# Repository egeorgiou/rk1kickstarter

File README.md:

# rk1kickstarter
RK1 Kickstarter Project

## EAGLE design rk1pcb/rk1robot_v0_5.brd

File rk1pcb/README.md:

rk1pcb
======

rk1 eagle pcb design

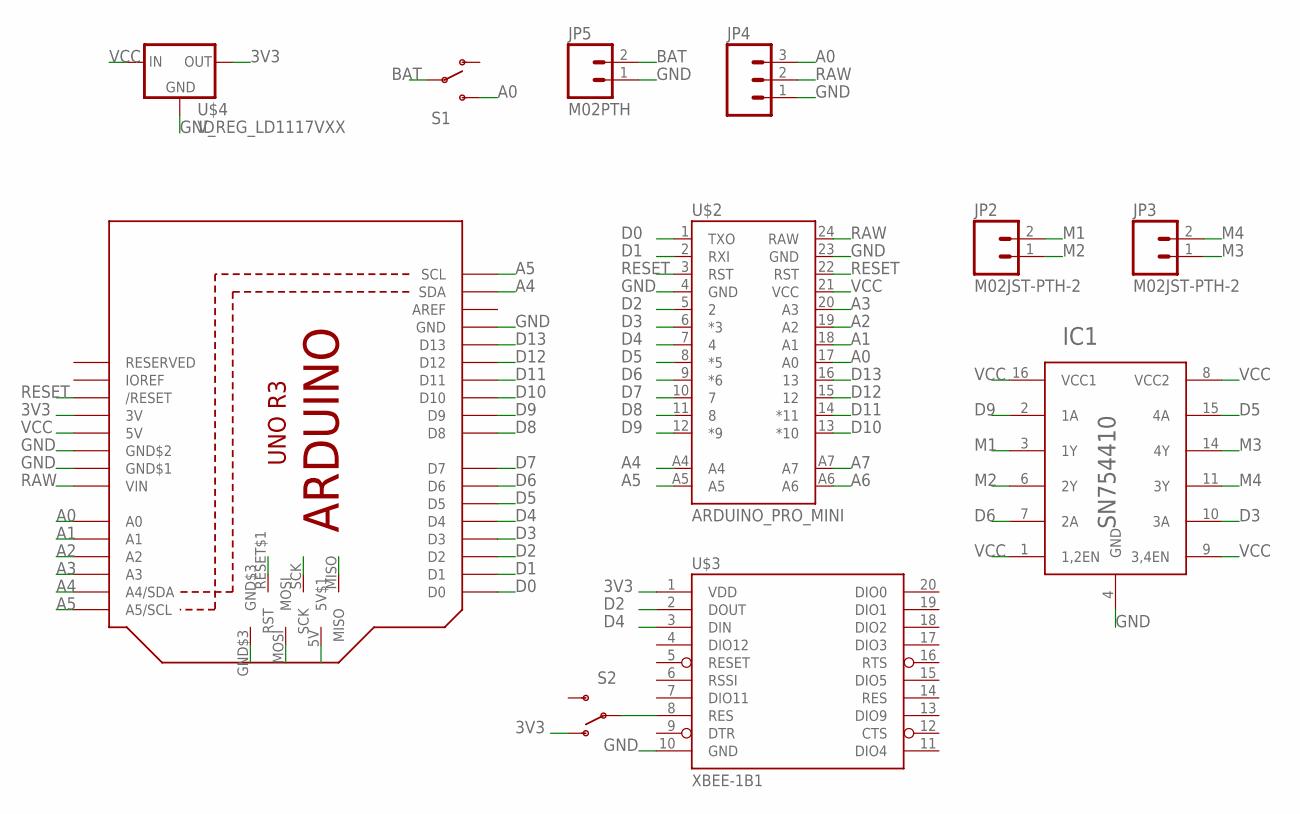
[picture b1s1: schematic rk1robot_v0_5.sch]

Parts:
IC1: SN754410; DIL16
JP2, JP3: M02JST-PTH-2; JST-2-PTH
JP4: M03PTH; 1X03
JP5: M02PTH; 1X02
S1, S2: SWITCH-SPDTPTH; SWITCH-SPDT
U$1: ARDUINO_R3_ICSP; ARDUINOR3_ICSP
U$2: ARDUINO_PRO_MINI
U$3: XBEE-1B1; XBEE-1
U$4: V_REG_LD1117VXX; 78XXL

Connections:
3V3: S2.1 (O), U$1.3V, U$3.1 (VDD), U$4.GND (OUT)
A0: JP4.3, S1.3 (S), U$1.A0, U$2.17 (A0)
A1: U$1.A1, U$2.18 (A1)
A2: U$1.A2, U$2.19 (A2)
A3: U$1.A3, U$2.20 (A3)
A4: U$1.A4 (A4/SDA), U$1.SDA, U$2.A4
A5: U$1.A5 (A5/SCL), U$1.SCL, U$2.A5
A6: U$2.A6
A7: U$2.A7
BAT: JP5.2, S1.2
D0: U$1.D0, U$2.1 (TXO)
D1: U$1.D1, U$2.2 (RXI)
D2: U$1.D2, U$2.5 (2), U$3.2 (DOUT)
D3: IC1.10 (3A), U$1.D3, U$2.6 (*3)
D4: U$1.D4, U$2.7 (4), U$3.3 (DIN)
D5: IC1.15 (4A), U$1.D5, U$2.8 (*5)
D6: IC1.7 (2A), U$1.D6, U$2.9 (*6)
D7: U$1.D7, U$2.10 (7)
D8: U$1.D8, U$2.11 (8)
D9: IC1.2 (1A), U$1.D9, U$2.12 (*9)
D10: U$1.D10, U$2.13 (*10)
D11: U$1.D11, U$1.MOSI, U$2.14 (*11)
D12: U$1.D12, U$1.MISO, U$2.15 (12)
D13: U$1.D13, U$1.SCK, U$2.16 (13)
GND: IC1.4 (GND), IC1.5 (GND), IC1.12 (GND), IC1.13 (GND), JP4.1, JP5.1, U$1.GND, U$1.GND$1, U$1.GND$2, U$1.GND$3, U$2.4 (GND), U$2.23 (GND), U$3.10 (GND), U$4.IN (GND)
M1: IC1.3 (1Y), JP2.2
M2: IC1.6 (2Y), JP2.1
M3: IC1.14 (4Y), JP3.1
M4: IC1.11 (3Y), JP3.2
unnamed: S2.2, U$3.8 (RES)
RAW: JP4.2, U$1.VIN, U$2.24 (RAW)
RESET: U$1.RESET (/RESET), U$1.RESET$1 (RST), U$2.3 (RST), U$2.22 (RST)
VCC: IC1.1 (1,2EN), IC1.8 (VCC2), IC1.9 (3,4EN), IC1.16 (VCC1), U$1.5V (5V$1), U$1.+5V (5V), U$2.21 (VCC), U$4.OUT (IN)

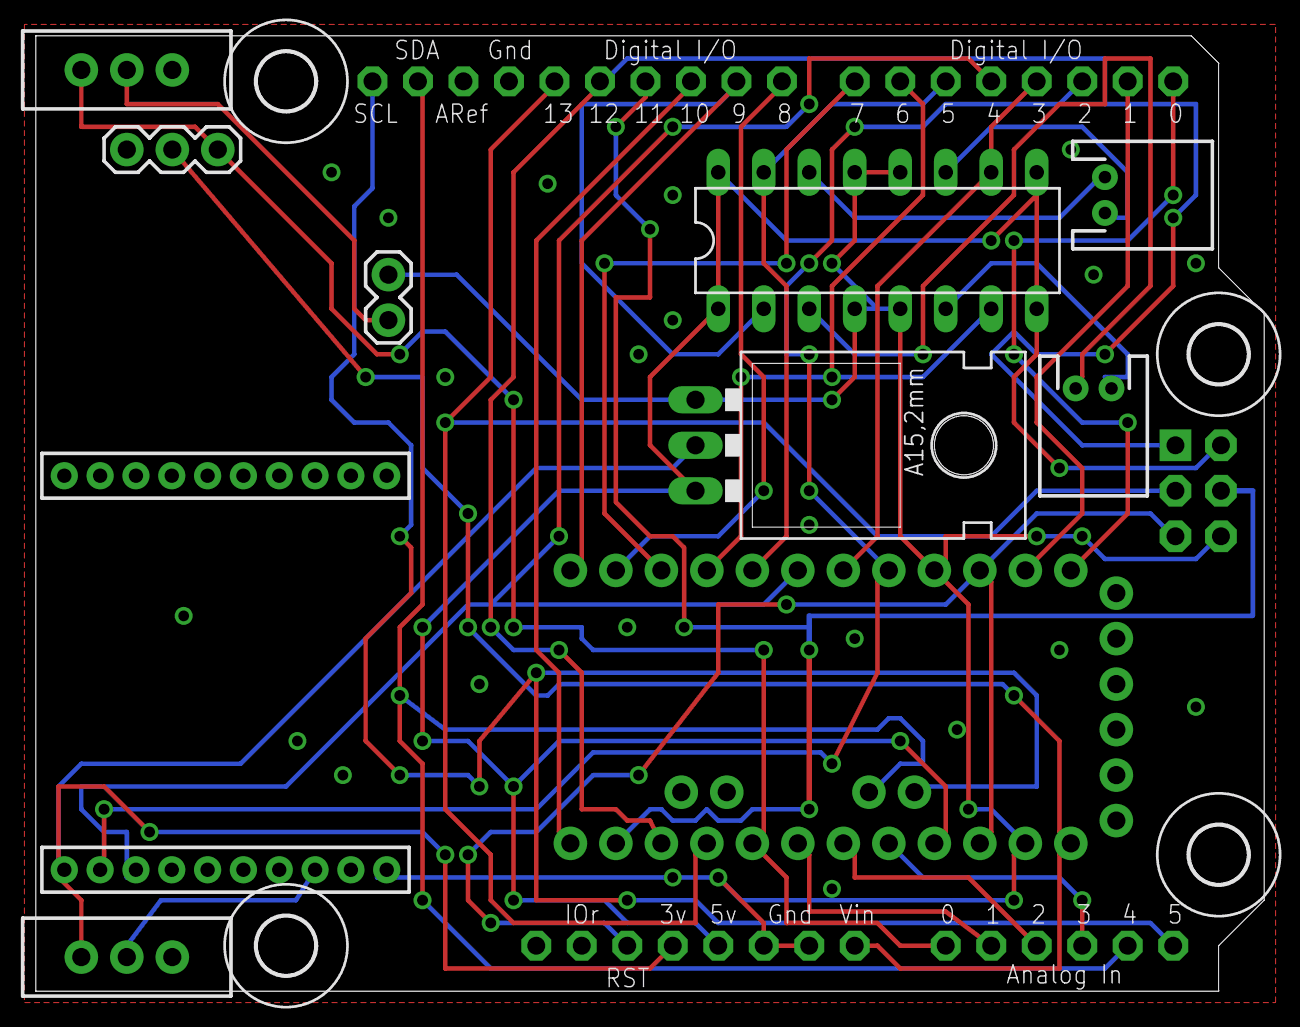
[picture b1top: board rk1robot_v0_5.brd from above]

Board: 2 copper layers, 68.6 x 53.3 mm, 15 parts (0 on the bottom side), 31 nets.

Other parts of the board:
U$5, U$6, U$7, U$8: 3,2

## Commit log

2015-04-08 setup

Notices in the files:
parts and their libraries:
SparkFun-Boards: Licensing: CC v3.0 Share-Alike You are welcome to use this library for commercial purposes.
